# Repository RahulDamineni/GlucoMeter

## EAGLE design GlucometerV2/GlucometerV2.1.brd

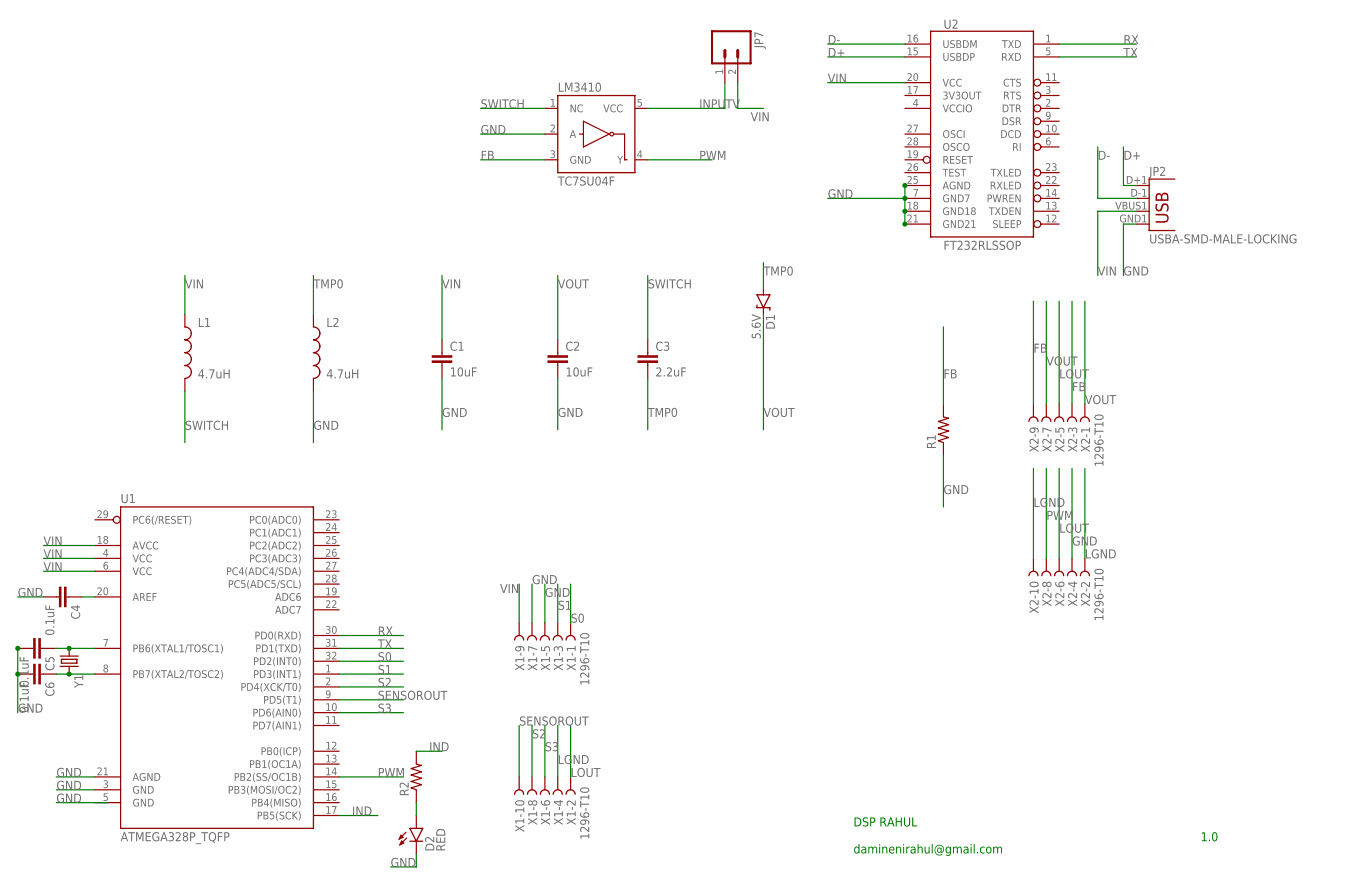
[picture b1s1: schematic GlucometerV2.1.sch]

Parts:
C1, C2: 10uF; 1206
C3: 2.2uF; 1206
C4, C5, C6: 0.1uF; 0603-CAP
D1: 5.6V; SOD-323
D2: RED; LED-1206
JP2: USBA-SMD-MALE-LOCKING; USB-A-SMT-MALE-LOCKING
JP7: M02POLAR_LOCK; MOLEX-1X2_LOCK
L1, L2: 4.7uH; 0603
LM3410: TC7SU04F; SOT23-5
R1, R2: RESISTOR1206; 1206
U1: ATMEGA328P_TQFP; TQFP32-08
U2: FT232RLSSOP; SSOP28DB
X1, X2: 1296-T10; 1296-10
Y1: CRYSTALHC49UV; HC49U-V

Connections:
D+: JP2.D+1 (D+), U2.15 (USBDP)
D-: JP2.D-1 (D-), U2.16 (USBDM)
FB: LM3410.3 (GND), R1.2, X2.3, X2.9
GND: C1.2, C2.2, C4.2, C5.2, C6.2, D2.C, JP2.GND1 (GND), L2.2, LM3410.2 (A), R1.1, U1.3 (GND), U1.21 (AGND), U2.7 (GND7), U2.18 (GND18), U2.21 (GND21), U2.25 (AGND), X1.5, X1.7, X2.4
IND: R2.2, U1.17 (PB5(SCK))
INPUTV: JP7.1, LM3410.5 (VCC)
LGND: X1.4, X2.2, X2.10
LOUT: X1.2, X2.5, X2.6
unnamed: C4.1, U1.20 (AREF)
unnamed: D2.A, R2.1
unnamed: C5.1, U1.7 (PB6(XTAL1/TOSC1)), Y1.1
unnamed: C6.1, U1.8 (PB7(XTAL2/TOSC2)), Y1.2
PWM: LM3410.4 (Y), U1.14 (PB2(SS/OC1B)), X2.8
RX: U1.30 (PD0(RXD)), U2.1 (TXD)
S0: U1.32 (PD2(INT0)), X1.1
S1: U1.1 (PD3(INT1)), X1.3
S2: U1.2 (PD4(XCK/T0)), X1.8
S3: U1.10 (PD6(AIN0)), X1.6
SENSOROUT: U1.9 (PD5(T1)), X1.10
SWITCH: C3.1, L1.2, LM3410.1 (NC)
TMP0: C3.2, D1.A, L2.1
TX: U1.31 (PD1(TXD)), U2.5 (RXD)
VCCIO: U2.4 (VCCIO)
VIN: C1.1, JP2.VBUS1 (VBUS), JP7.2, L1.1, U1.4 (VCC), U1.6 (VCC), U1.18 (AVCC), U2.20 (VCC), X1.9
VOUT: C2.1, D1.C, X2.1, X2.7

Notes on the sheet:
DSP RAHUL daminenirahul@gmail.com
1.0

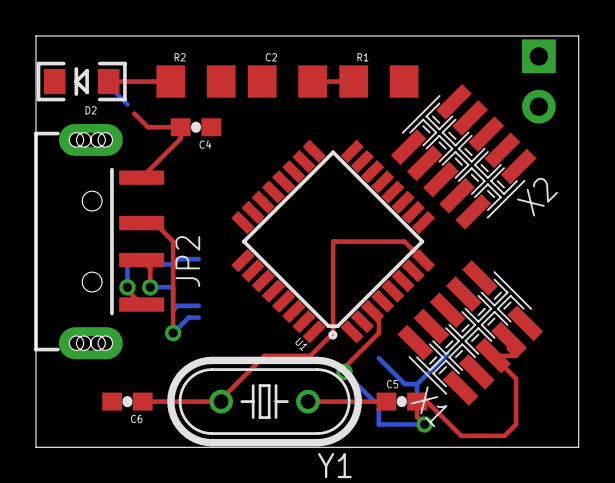
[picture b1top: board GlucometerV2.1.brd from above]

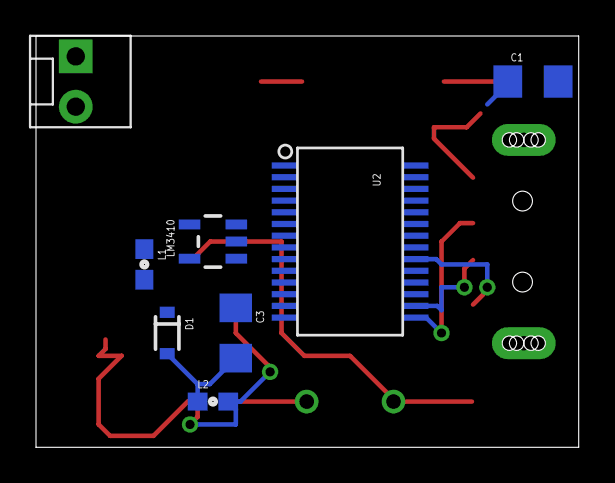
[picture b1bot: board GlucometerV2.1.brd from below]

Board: 2 copper layers, 30.1 x 22.8 mm, 20 parts (8 on the bottom side), 24 nets.

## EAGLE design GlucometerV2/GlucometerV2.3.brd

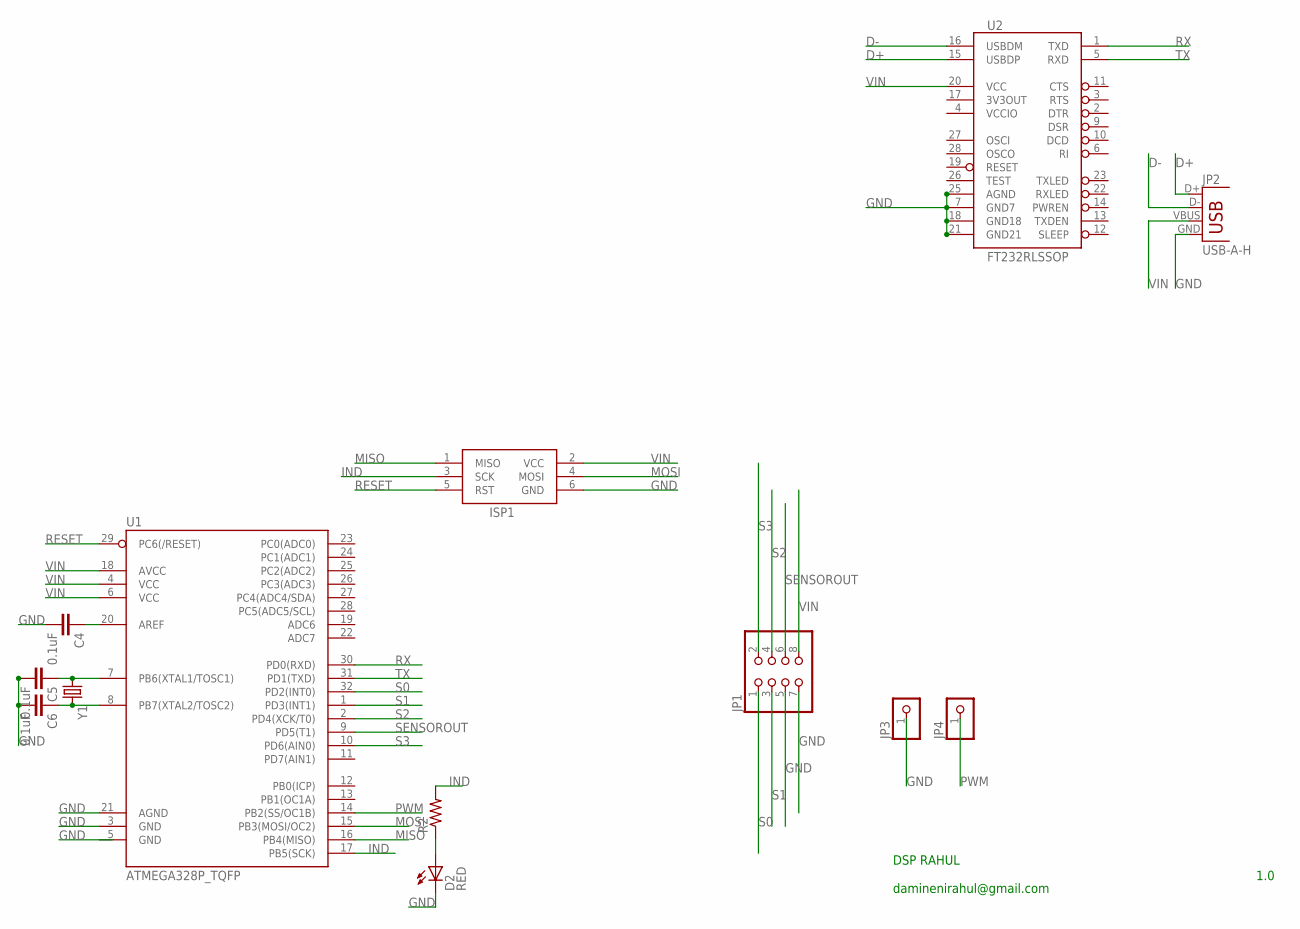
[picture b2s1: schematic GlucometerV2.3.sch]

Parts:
C4, C5, C6: 0.1uF; 0603-CAP
D2: RED; CHIPLED_1206
ISP1: AVRISP-6; AVRISP
JP1: PINHD-2X4; 2X04
JP2: USB-A-H
JP3, JP4: PINHD-1X1; 1X01
R2: RESISTOR1206; 1206
U1: ATMEGA328P_TQFP; TQFP32-08
U2: FT232RLSSOP; SSOP28DB
Y1: CRYSTALHC49UV; HC49U-V

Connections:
D+: JP2.D+, U2.15 (USBDP)
D-: JP2.D-, U2.16 (USBDM)
GND: C4.2, C5.2, C6.2, D2.C, ISP1.6 (GND), JP1.5, JP1.7, JP2.GND, JP3.1, U1.3 (GND), U1.21 (AGND), U2.7 (GND7), U2.18 (GND18), U2.21 (GND21), U2.25 (AGND)
IND: ISP1.3 (SCK), R2.2, U1.17 (PB5(SCK))
MISO: ISP1.1 (MISO), U1.16 (PB4(MISO))
MOSI: ISP1.4 (MOSI), U1.15 (PB3(MOSI/OC2))
unnamed: C4.1, U1.20 (AREF)
unnamed: D2.A, R2.1
unnamed: C5.1, U1.7 (PB6(XTAL1/TOSC1)), Y1.1
unnamed: C6.1, U1.8 (PB7(XTAL2/TOSC2)), Y1.2
PWM: JP4.1, U1.14 (PB2(SS/OC1B))
RESET: ISP1.5 (RST), U1.29 (PC6(/RESET))
RX: U1.30 (PD0(RXD)), U2.1 (TXD)
S0: JP1.1, U1.32 (PD2(INT0))
S1: JP1.3, U1.1 (PD3(INT1))
S2: JP1.4, U1.2 (PD4(XCK/T0))
S3: JP1.2, U1.10 (PD6(AIN0))
SENSOROUT: JP1.6, U1.9 (PD5(T1))
TX: U1.31 (PD1(TXD)), U2.5 (RXD)
VCCIO: U2.4 (VCCIO)
VIN: ISP1.2 (VCC), JP1.8, JP2.VBUS, U1.4 (VCC), U1.6 (VCC), U1.18 (AVCC), U2.20 (VCC)

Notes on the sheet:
DSP RAHUL daminenirahul@gmail.com
1.0

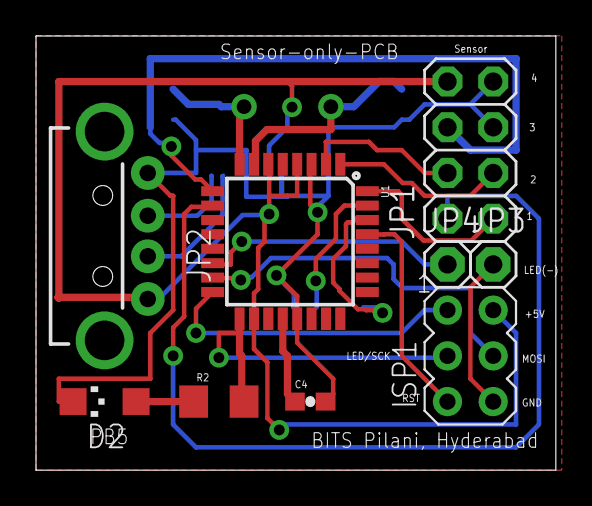
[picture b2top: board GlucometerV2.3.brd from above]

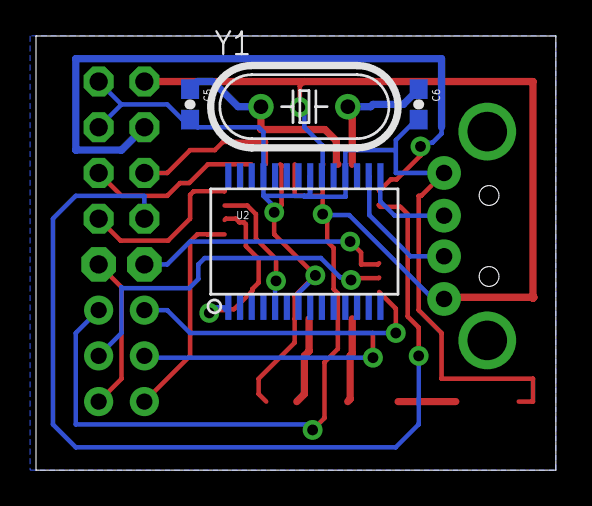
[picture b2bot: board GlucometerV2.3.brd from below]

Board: 2 copper layers, 28.9 x 24.1 mm, 13 parts (4 on the bottom side), 20 nets.

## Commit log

2016-02-05 :lollipop: Added .gitattributes & .gitignore files
2016-02-05 Content Merged
    Take a look at GlucometerV2.3.sch

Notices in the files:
parts and their libraries:
SparkFun-Passives: Licensing: Creative Commons ShareAlike 4.0 International - https://creativecommons.org/licenses/by-sa/4.0
